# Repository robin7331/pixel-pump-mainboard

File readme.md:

# Pixel Pump Mainboard Rev 8
`KiCad 6.0.11`

See iBOM [rendered as Page](https://htmlpreview.github.io/?https://github.com/robin7331/pixel-pump-mainboard/blob/main/bom/ibom.html) via GitHub Pages

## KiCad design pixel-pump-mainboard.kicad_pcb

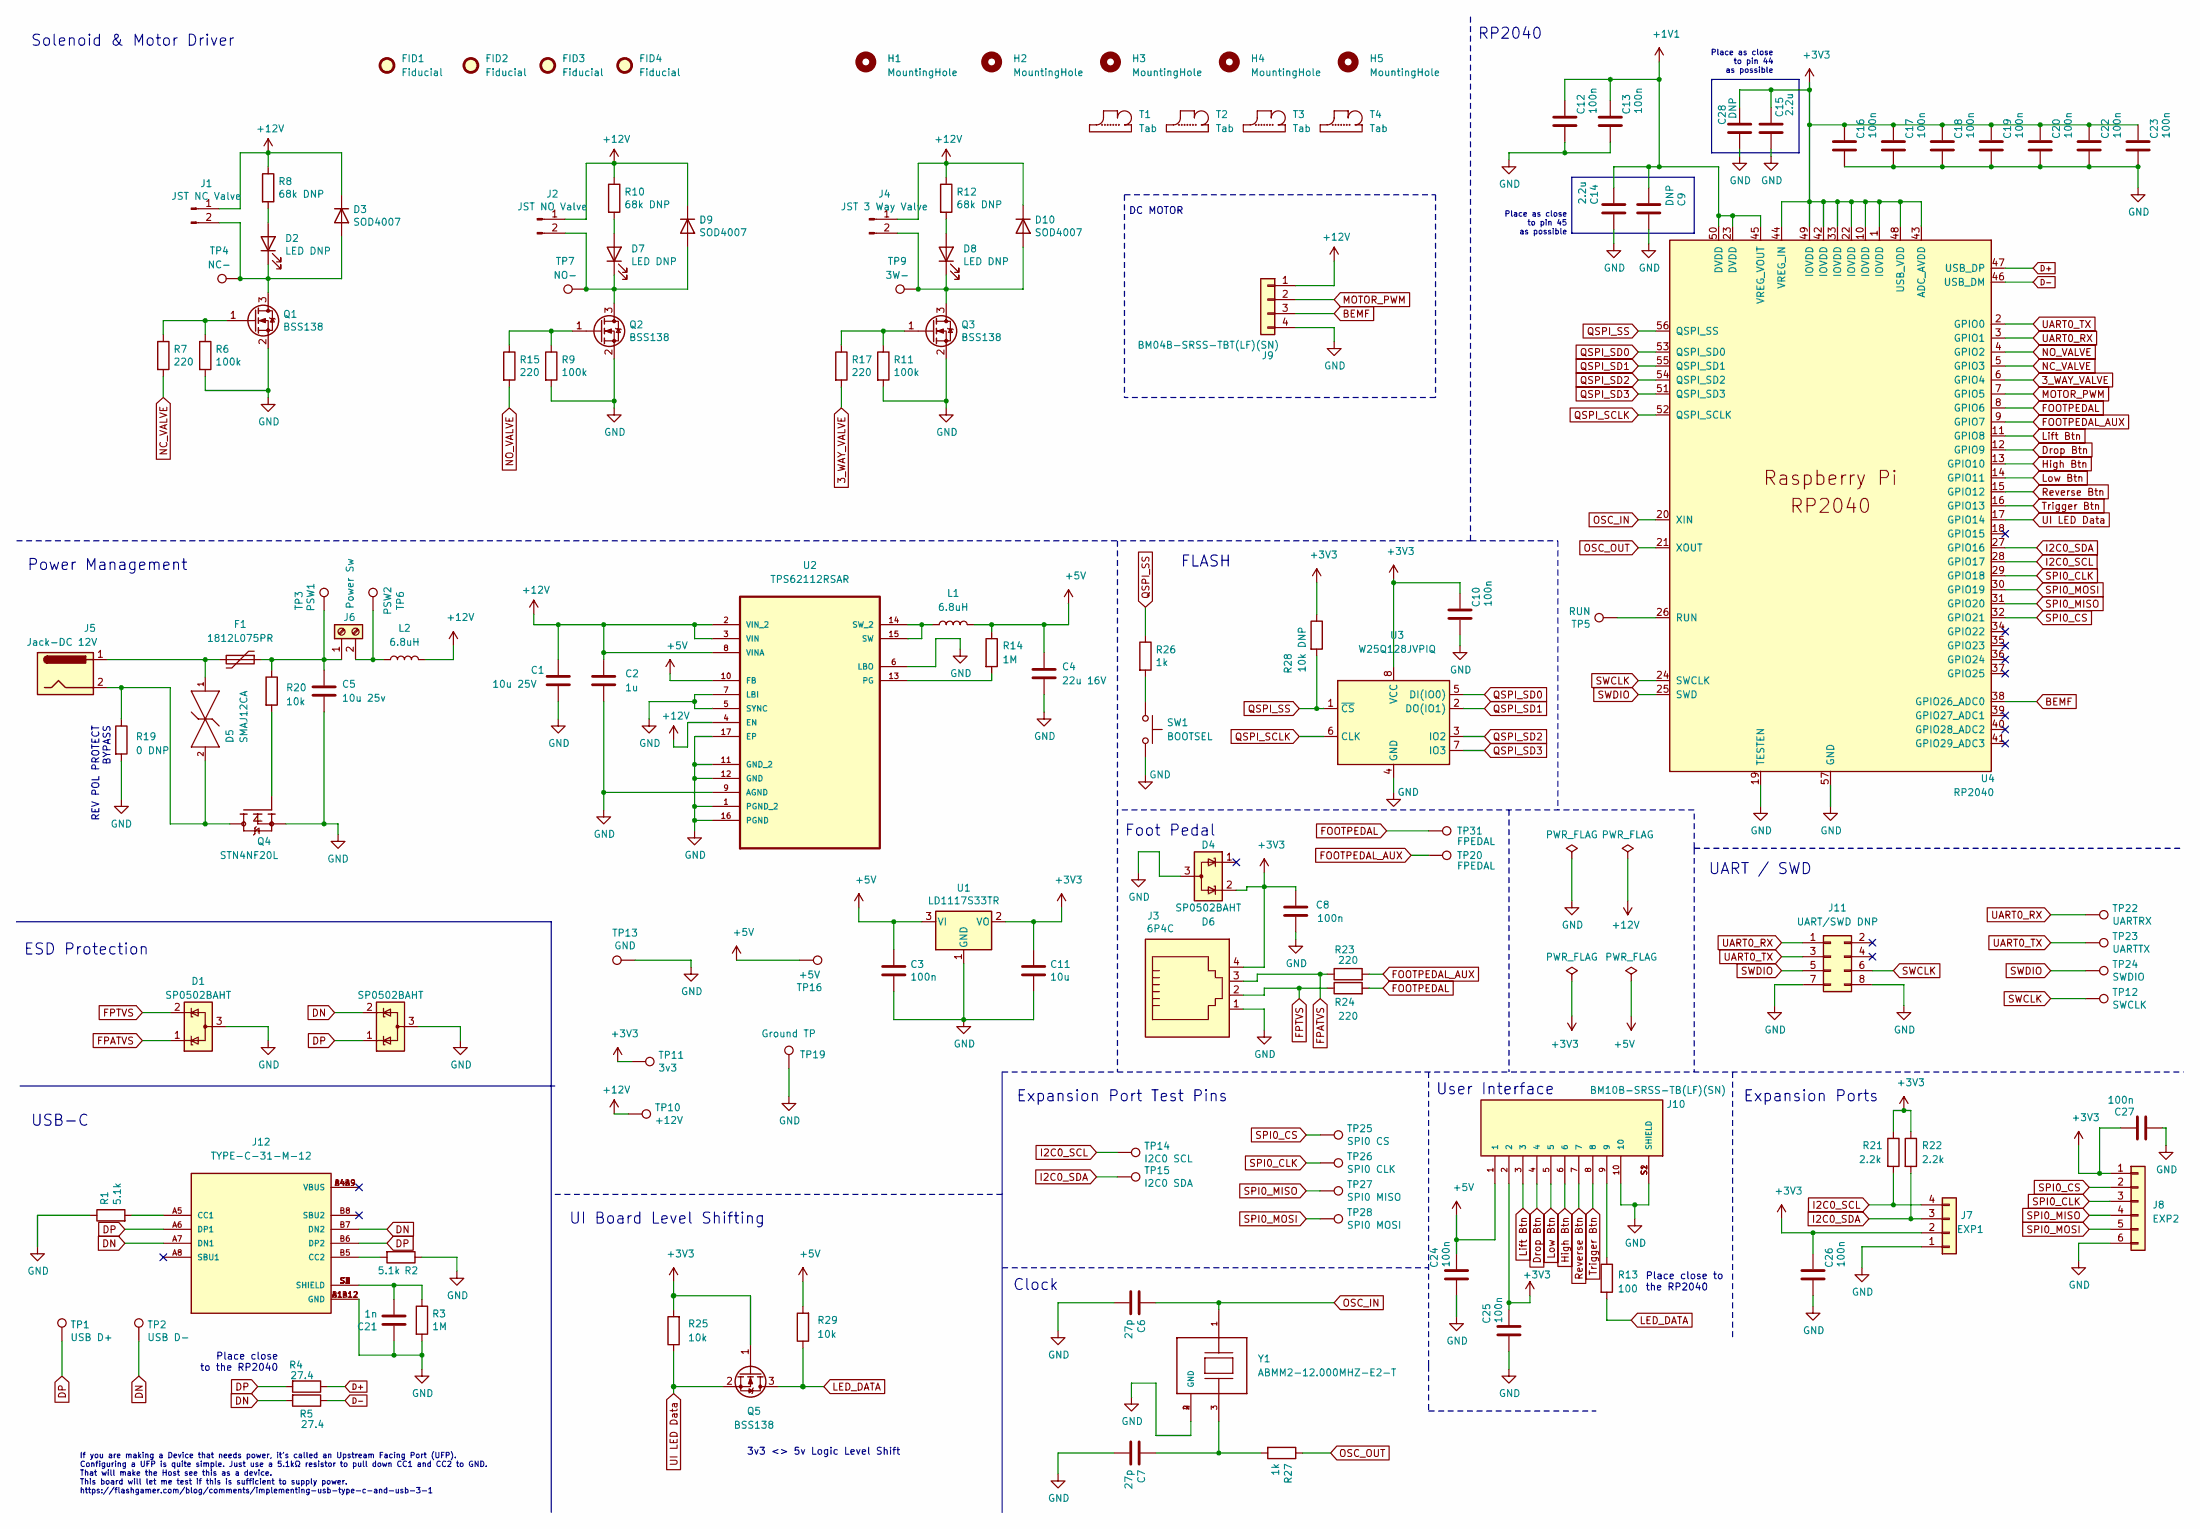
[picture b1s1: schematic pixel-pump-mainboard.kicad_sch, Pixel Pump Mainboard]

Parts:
C1: 10u 25V; C_1210_3225Metric; Part Number C3225X5R1E106K
C2: 1u; C_0805_2012Metric; MPN 1u 0805
C3, C8, C24, C25, C26, C27: 100n; C_0603_1608Metric; MPN 100n 0603
C4: 22u 16V; C_1210_3225Metric; MPN C3225X7R1C226M250AC
C5: 10u 25v; C_1210_3225Metric; Part C3225X5R1E106K
C6, C7: 27p; C_0603_1608Metric; MPN 27p 0603
C9, C28: DNP; C_0402_1005Metric; MPN DNP
C10, C12, C13, C16, C17, C18, C19, C20, C22, C23: 100n; C_0402_1005Metric; MPN 100n 0402
C11: 10u; C_0603_1608Metric; MPN 10u 0603
C14, C15: 2.2u; C_0402_1005Metric; MPN 2.2u 0402
C21: 1n; C_0603_1608Metric; MPN 1n 0603
D1, D4, D6: SP0502BAHT; SOT-23; MPN SP0502BAHT
D2, D7, D8: LED DNP; LED_0603_1608Metric; MPN ORH-G36G DNP
D3, D9, D10: SOD4007; D_SOD-123F; MPN SOD4007
D5: SMAJ12CA; D_SMA; breakdown voltage 13.3V; clamping voltage 19.9V; mouser part number 576-SMAJ12CA; digikey description TVS DIODE 12V 19.9V DO214AC
F1: 1812L075PR; Fuse_1812_4532Metric; MPN 1812L075PR
FID1, FID2, FID3, FID4: Fiducial; Fiducial_0.75mm_Mask1.5mm
H1, H2, H3, H4, H5: MountingHole; MountingHole_3.2mm_M3_Pad_Via
J1: JST NC Valve; JST_XH_B2B-XH-A_1x02_P2.50mm_Vertical; MPN B2B-XH-A-GU
J2: JST NO Valve; JST_XH_B2B-XH-A_1x02_P2.50mm_Vertical; MPN B2B-XH-A-GU
J3: 6P4C; RJ14_Connfly_DS1133-S4_Horizontal; MPN DS1133-S40BPX
J4: JST 3 Way Valve; JST_XH_B2B-XH-A_1x02_P2.50mm_Vertical; MPN B2B-XH-A-GU
J5: Jack-DC 12V; BarrelJack_Wuerth_6941xx301002; MPN 694106301002
J6: Power Sw; TerminalBlock_Phoenix_MKDS-1,5-2-5.08_1x02_P5.08mm_Horizont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; MPN WJ500V-5.08-2P
J7: EXP1; BM04B-SRSS-TBT; MPN BM04B-SRSS-TB(LF)(SN)
J8: EXP2; BM06B-SRSS-TBT; MPN BM06B-SRSS-TB(LF)(SN)
J9: BM04B-SRSS-TBT(LF)(SN); BM04B-SRSS-TBT; MPN BM04B-SRSS-TBT(LF)(SN)
J10: BM10B-SRSS-TB(LF)(SN); PARTREV N/A
J11: UART/SWD DNP; PinHeader_2x04_P2.00mm_Vertical; MPN DNP
J12: TYPE-C-31-M-12; HRO_TYPE-C-31-M-12; PARTREV A
L1, L2: 6.8uH; L_TDK_SLF7032; MPN SLF7032T-6R8M1R6-2-PF
Q1, Q2, Q3: BSS138; SOT-23; MPN BSS138P
Q4: STN4NF20L; SOT223; PARTNO 497-10779-1-ND
Q5: BSS138; SOT-23; MPN BSS138
R1: 5.1k; R_0603_1608Metric; MPN 5.1k 0402
R2: 5.1k; R_0603_1608Metric; MPN 5.1k 0603
R3, R14: 1M; R_0603_1608Metric; MPN 1M 0603
R4, R5: 27.4; R_0402_1005Metric; MPN 27.4 0402
R6, R9, R11: 100k; R_0603_1608Metric; MPN 100k 0603
R7, R15, R17, R23, R24: 220; R_0603_1608Metric; MPN 220 0603
R8, R10, R12: 68k DNP; R_0603_1608Metric; MPN 68k 0603 DNP
R13: 100; R_0603_1608Metric; MPN 100 0603
R19: 0 DNP; R_0805_2012Metric; MPN 0 0805 DNP
R20, R25, R29: 10k; R_0603_1608Metric; MPN 10k 0603
R21, R22: 2.2k; R_0603_1608Metric; MPN 2.2k 0603
R26, R27: 1k; R_0603_1608Metric; MPN 1k 0603
R28: 10k DNP; R_0603_1608Metric; MPN 10k 0603 DNP
SW1: BOOTSEL; SW_Tactile_SKHH_Angled; MPN 1825027-5
T1, T2, T3, T4: Tab
TP1: USB D+; TestPoint_Pad_D2.0mm
TP2: USB D-; TestPoint_Pad_D2.0mm
TP3: PSW1; TestPoint_Pad_D2.0mm
TP4: NC-; TestPoint_Pad_D2.0mm
TP5: RUN; TestPoint_Pad_D2.0mm
TP6: PSW2; TestPoint_Pad_D2.0mm
TP7: NO-; TestPoint_Pad_D2.0mm
TP9: 3W-; TestPoint_Pad_D2.0mm
TP10: +12V; TestPoint_Pad_D2.0mm
TP11: 3v3; TestPoint_Pad_D2.0mm
TP12: SWCLK; TestPoint_Pad_D2.0mm
TP13: GND; TestPoint_Pad_D2.0mm
TP14: I2C0 SCL; TestPoint_Pad_D2.0mm
TP15: I2C0 SDA; TestPoint_Pad_D2.0mm
TP16: +5V; TestPoint_Pad_D2.0mm
TP19: Ground TP; TestPoint_Keystone_5010-5014_Multipurpose
TP20, TP31: FPEDAL; TestPoint_Pad_D2.0mm
TP22: UARTRX; TestPoint_Pad_D2.0mm
TP23: UARTTX; TestPoint_Pad_D2.0mm
TP24: SWDIO; TestPoint_Pad_D2.0mm
TP25: SPI0 CS; TestPoint_Pad_D2.0mm
TP26: SPI0 CLK; TestPoint_Pad_D2.0mm
TP27: SPI0 MISO; TestPoint_Pad_D2.0mm
TP28: SPI0 MOSI; TestPoint_Pad_D2.0mm
U1: LD1117S33TR; SOT-223; MPN LD1117S33TR
U2: TPS62112RSAR; QFN65P400X400X100-17N; MPN TPS62112RSAR
U3: W25Q128JVPIQ; SON127P500X600X80-9N; MPN W25Q128JVPIQ
U4: RP2040; RP2040-QFN-56; MPN RP2040
Y1: ABMM2-12.000MHZ-E2-T; XTAL_ABMM2-12.000MHZ-E2-T; PARTREV 01.18.13

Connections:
3_WAY_VALVE: R17.2, U4.6 (GPIO4)
+1V1: C9.1, C12.2, C13.2, C14.1, U4.23 (DVDD), U4.45 (VREG_VOUT), U4.50 (DVDD)
+3V3: C8.2, C10.2, C11.1, C15.1, C16.2, C17.2, C18.2, C19.2, C20.2, C22.2, C23.2, C25.2, C26.2, C27.2, C28.1, D6.2 (K), J3.4, J7.2, J8.1, J10.2, Q5.1 (G), R21.1, R22.1, R25.2, R28.1, TP11.1, U1.2 (VO), U3.8 (VCC), U4.1 (IOVDD), U4.10 (IOVDD), U4.22 (IOVDD), U4.33 (IOVDD), U4.42 (IOVDD), U4.43 (ADC_AVDD), U4.44 (VREG_IN), U4.48 (USB_VDD), U4.49 (IOVDD)
+5V: C3.1, C4.1, C24.2, J10.1, L1.2, R14.1, R29.2, TP16.1, U1.3 (VI), U2.10 (FB)
+12V: C1.1, C2.1, D3.1 (K), D9.1 (K), D10.1 (K), J1.1, J2.1, J4.1, J9.1, L2.2, R8.1, R10.1, R12.1, TP10.1, U2.2 (VIN_2), U2.3 (VIN), U2.4 (EN), U2.8 (VINA)
BEMF: J9.3, U4.38 (GPIO26_ADC0)
D+: R4.1, U4.47 (USB_DP)
D-: R5.1, U4.46 (USB_DM)
DN: D4.2 (K), J12.A7 (DN1), J12.B7 (DN2), R5.2, TP2.1
DP: D4.1 (K), J12.A6 (DP1), J12.B6 (DP2), R4.2, TP1.1
Drop Btn: J10.4, U4.12 (GPIO9)
FOOTPEDAL: R24.2, TP31.1, U4.8 (GPIO6)
FOOTPEDAL_AUX: R23.2, TP20.1, U4.9 (GPIO7)
FPATVS: D1.1 (K), J3.3, R23.1
FPTVS: D1.2 (K), J3.2, R24.1
GND: C1.2, C2.2, C3.2, C4.2, C5.2, C6.2, C7.2, C8.1, C9.2, C10.1, C11.2, C12.1, C13.1, C14.2, C15.2, C16.1, C17.1, C18.1, C19.1, C20.1, C21.1, C22.1, C23.1, C24.1, C25.1, C26.1, C27.1, C28.2, D1.3 (A), D4.3 (A), D6.3 (A), J3.1, J7.1, J8.6, J9.4, J10.10, J10.S1 (SHIELD), J10.S2 (SHIELD), J11.7, J11.8, J12.A1B12 (GND), J12.B1A12 (GND), Q1.2 (S), Q2.2 (S), Q3.2 (S), Q4.3, R1.1, R2.1, R3.2, R6.2, R9.2, R11.2, R19.2, SW1.2, TP13.1, TP19.1, U1.1 (GND), U2.1 (PGND_2), U2.5 (SYNC), U2.6 (LBO), U2.7 (LBI), U2.9 (AGND), U2.11 (GND_2), U2.12 (GND), U2.16 (PGND), U2.17 (EP), U3.4 (GND), U4.19 (TESTEN), U4.57 (GND), Y1.2 (GND), Y1.4 (GND)
High Btn: J10.6, U4.13 (GPIO10)
I2C0_SCL: J7.4, R21.2, TP14.1, U4.28 (GPIO17)
I2C0_SDA: J7.3, R22.2, TP15.1, U4.27 (GPIO16)
LED_DATA: Q5.3 (D), R13.2, R29.1
Lift Btn: J10.3, U4.11 (GPIO8)
Low Btn: J10.5, U4.14 (GPIO11)
MOTOR_PWM: J9.2, U4.7 (GPIO5)
NC_VALVE: R7.2, U4.5 (GPIO3)
NO_VALVE: R15.2, U4.4 (GPIO2)
unnamed: C5.1, F1.1, J6.1, R20.1, TP3.1
unnamed: C7.1, R27.2, Y1.3
unnamed: C21.2, J12.S1 (SHIELD), J12.S2 (SHIELD), J12.S3 (SHIELD), J12.S4 (SHIELD), R3.1
unnamed: D2.1 (K), D3.2 (A), J1.2, Q1.3 (D), TP4.1
unnamed: D2.2 (A), R8.2
unnamed: D5.1, F1.2, J5.1
unnamed: D5.2, J5.2, Q4.2, Q4.T, R19.1
unnamed: D7.1 (K), D9.2 (A), J2.2, Q2.3 (D), TP7.1
unnamed: D7.2 (A), R10.2
unnamed: D8.2 (A), R12.2
unnamed: D8.1 (K), D10.2 (A), J4.2, Q3.3 (D), TP9.1
unnamed: J6.2, L2.1, TP6.1
unnamed: J10.9, R13.1
unnamed: J12.A5 (CC1), R1.2
unnamed: J12.B5 (CC2), R2.2
unnamed: L1.1, U2.14 (SW_2), U2.15 (SW)
unnamed: Q1.1 (G), R6.1, R7.1
unnamed: Q2.1 (G), R9.1, R15.1
unnamed: Q3.1 (G), R11.1, R17.1
unnamed: Q4.1, R20.2
unnamed: R14.2, U2.13 (PG)
unnamed: R26.2, SW1.1
unnamed: TP5.1, U4.26 (RUN)
OSC_IN: C6.1, U4.20 (XIN), Y1.1
OSC_OUT: R27.1, U4.21 (XOUT)
QSPI_SCLK: U3.6 (CLK), U4.52 (QSPI_SCLK)
QSPI_SD0: U3.5 (DI(IO0)), U4.53 (QSPI_SD0)
QSPI_SD1: U3.2 (DO(IO1)), U4.55 (QSPI_SD1)
QSPI_SD2: U3.3 (IO2), U4.54 (QSPI_SD2)
QSPI_SD3: U3.7 (IO3), U4.51 (QSPI_SD3)
QSPI_SS: R26.1, R28.2, U3.1 (~CS), U4.56 (QSPI_SS)
Reverse Btn: J10.7, U4.15 (GPIO12)
SPI0_CLK: J8.3, TP26.1, U4.29 (GPIO18)
SPI0_CS: J8.2, TP25.1, U4.32 (GPIO21)
SPI0_MISO: J8.4, TP27.1, U4.31 (GPIO20)
SPI0_MOSI: J8.5, TP28.1, U4.30 (GPIO19)
SWCLK: J11.6, TP12.1, U4.24 (SWCLK)
SWDIO: J11.5, TP24.1, U4.25 (SWD)
Trigger Btn: J10.8, U4.16 (GPIO13)
UART0_RX: J11.1, TP22.1, U4.3 (GPIO1)
UART0_TX: J11.3, TP23.1, U4.2 (GPIO0)
UI LED Data: Q5.2 (S), R25.1, U4.17 (GPIO14)

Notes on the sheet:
ESD Protection
FLASH
Clock
REV POL PROTECT BYPASS
DC MOTOR
Place close to the RP2040
UART / SWD
Expansion Port Test Pins
Place as close to pin 45 as possible
Power Management
Solenoid & Motor Driver
RP2040
User Interface
Place close to the RP2040
If you are making a Device that needs power, it’s called an Upstream Facing Port (UFP). Configuring a UFP is quite simple. Just use a 5.1kΩ resistor to pull down CC1 and CC2 to GND. That will make the Host see this as a device. This board will let me test if this is sufficient to supply power. http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
UI Board Level Shifting
3v3 <> 5v Logic Level Shift
Foot Pedal
USB-C
Place as close to pin 44 as possible
Expansion Ports

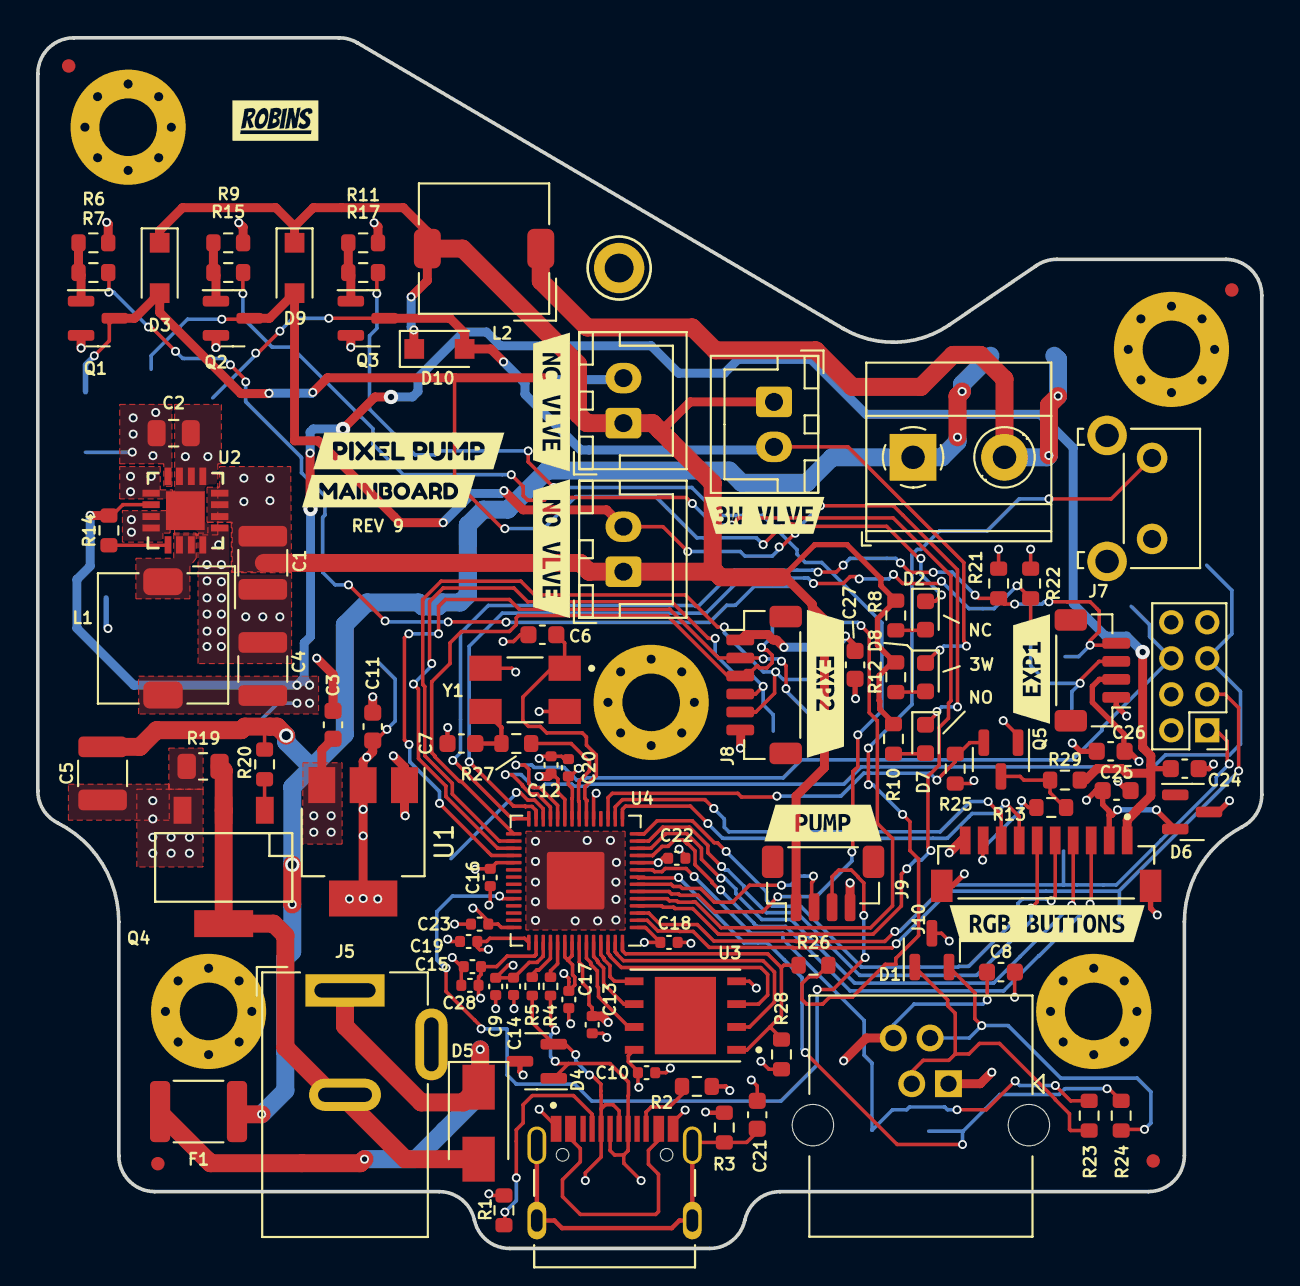
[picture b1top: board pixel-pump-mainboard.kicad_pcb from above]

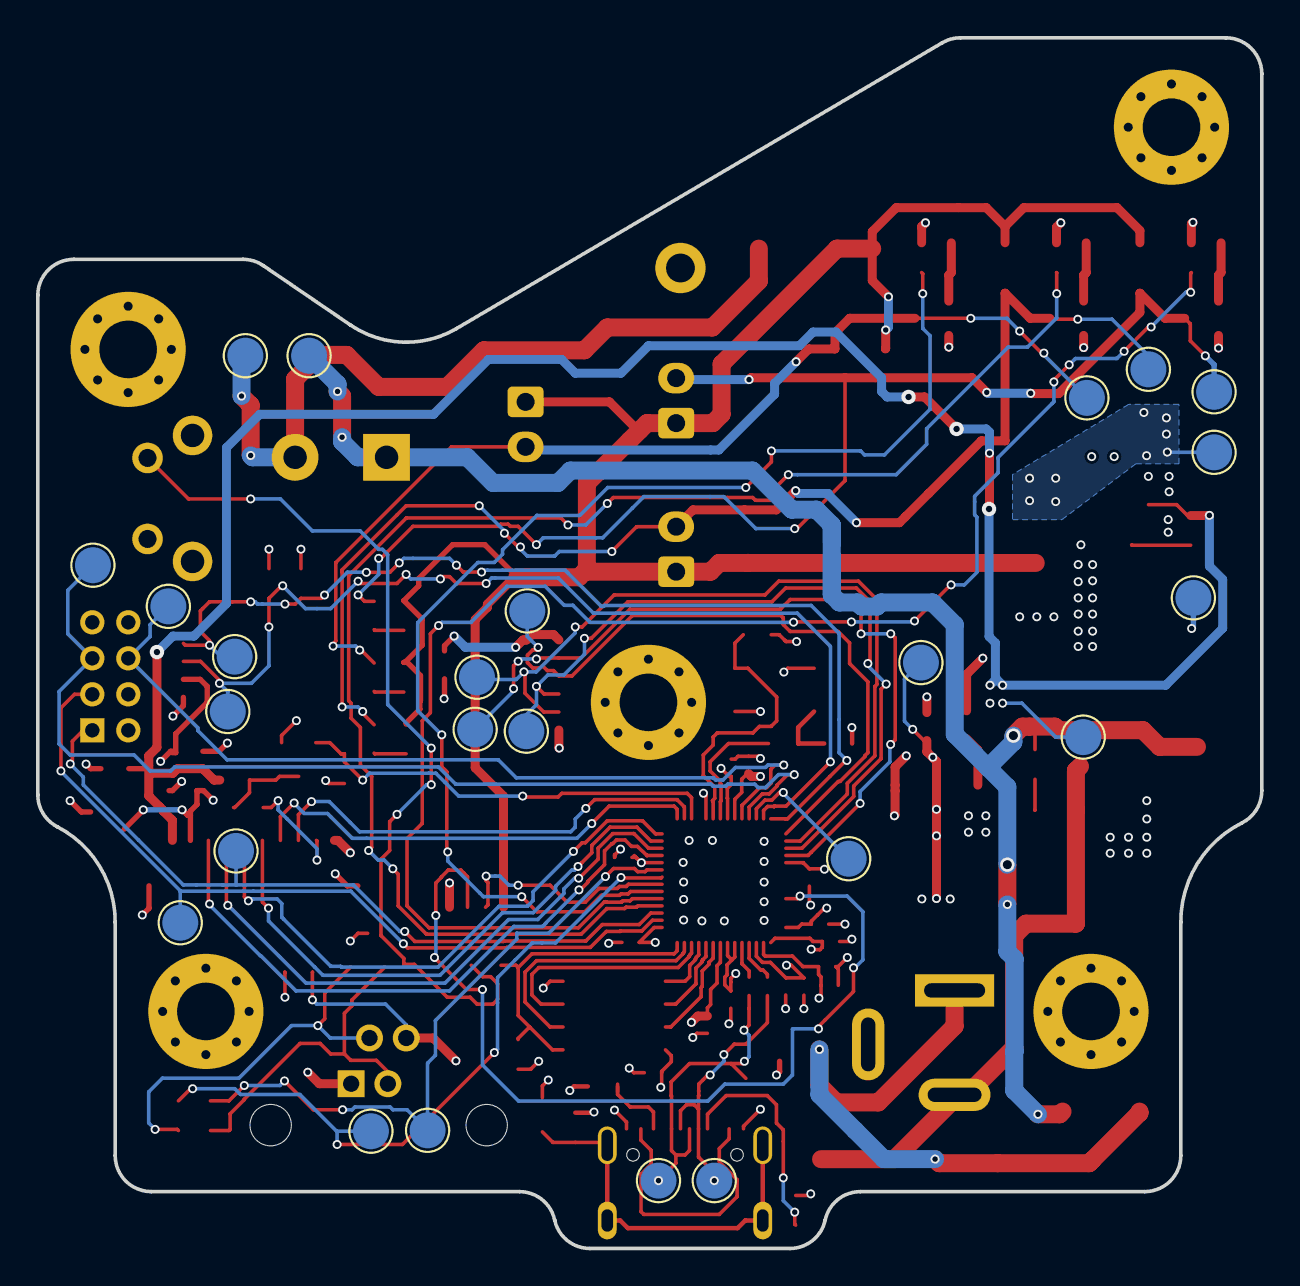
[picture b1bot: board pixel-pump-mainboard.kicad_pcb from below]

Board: 4 copper layers, 68.0 x 67.3 mm, 138 parts (24 on the bottom side), 67 nets.

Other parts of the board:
kibuzzard-62EBC211: G***; kibuzzard-62EBC211
kibuzzard-62EBC230: G***; kibuzzard-62EBC230
kibuzzard-626BB8E0: G***; kibuzzard-626BB8E0
kibuzzard-626BB906: G***; kibuzzard-626BB906
kibuzzard-6107E0E1: G***; kibuzzard-6107E0E1
kibuzzard-6107E4A2: G***; kibuzzard-6107E4A2
kibuzzard-6107E44E: G***; kibuzzard-6107E44E
kibuzzard-6107E45C: G***; kibuzzard-6107E45C
kibuzzard-6107E302: G***; kibuzzard-6107E302

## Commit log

2020-12-17 initial
2020-12-17 added gitignore
2020-12-18 schematics finished
2020-12-21 schematics done
2020-12-22 another wip
2020-12-22 routing finished
2020-12-22 added molex
2020-12-22 last changes and gerber files generated
2020-12-22 added ibom
2021-01-14 Ignore step files
2021-01-14 Cleanup values
2021-01-14 Fix wrong boost feedback voltage divider resistors
2021-01-14 Dim LEDs by increasing their resistor values
2021-01-14 Fix both fuse footprints (they were swapped)
2021-01-14 Generate iBom
2021-01-14 Update silkscreen labels
2021-03-03 Add DXF files from fusion
2021-03-08 remove old files
2021-03-08 Add backups to .gitignore
2021-03-08 Finished schematics
2021-03-09 finished schematics and assigned footprints
2021-03-09 Remove old PCB
2021-03-09 Initial PCB
2021-03-09 Update USB-C
2021-03-09 Updated PCB
2021-03-09 Edge cuts update
2021-03-09 Placed components
2021-03-09 pcb layout finished
2021-03-09 Adjusted board thickness to be 1.6mm
2021-03-10 Generate gerbers
2021-03-11 Generated Gerbers
2021-03-27 Create schematic PDF
2021-05-17 STM32 version
2021-05-17 Change DC-DC 5V converter to TPS561201DDCR
2021-05-17 Change from STM32 to RP2040
2021-05-17 Cleanup
2021-05-17 Assign or update remaining footprints
2021-05-17 Update crystal and footprints of components
2021-05-19 RP2040 PCB routed
2021-05-19 Add fiducials
2021-05-20 Updated min via drill and pad size
2021-08-02 Change various things
2021-08-02 Bump rev to 2
2021-08-02 Assign footprints
2021-08-02 WiP updating footprints
2021-08-02 Updated kicad nightly
2021-08-02 WiP Layout Ref 2
2021-08-02 Finished Ref 2 layout
2021-08-02 Update passives around RP2040
2021-08-02 Add UI board level shifting
2021-08-02 Updated pad below RP2040
2021-08-03 Changed Buck Converter
2021-08-03 Add missing components
2021-08-03 Minor upgrades
2021-08-03 Remove old schematics
2021-08-03 Add dxf import documentation
2021-08-03 Plot board
2021-08-03 Update footprints and generate new iBOM
2021-08-06 Changed part no and regenerated iBOM
2021-08-06 Generate rev 2 gerbers
2021-11-19 Rename entire project to pixel pump
2021-11-19 Clean footprint library
2021-11-19 Cleanup board libraries
2021-11-19 Remove old dependency
2021-11-19 Add readme
2021-11-21 Add PDF/PNG schematic
2022-01-10 Upgrade to Kicad 6
2022-01-11 Updated schematic for EMI compliance
2022-01-11 Minor Rev 3 changes
2022-01-11 Minor things fixed
2022-01-12 ERC & Assigned footprints
2022-01-12 Updated layout for EMI specific changes
2022-01-14 Finish EMI changes
2022-01-14 Remove old gerbers
2022-01-14 Add panel-output to gitignore
2022-01-14 Update iBOM
2022-01-14 Adjusted spacing between testpoints
2022-01-14 Add panelize scripts
2022-01-14 Update gitignore
2022-01-15 Update panel script
2022-01-15 Add automatic gerber creation to build scriot
2022-01-16 Cleanup dxf files
2022-01-16 Remove rescue lib and dcm
2022-04-29 Rename ports to EXP1 and EXP2 and reduce mousebite stiffness
2022-05-23 Switch to CTS 445C25D12M00000 12 MHz crystal
2022-07-25 Revert back to ABM12 footprint
2022-08-04 Assign all MPNs
2022-08-04 Add robins logo
2022-08-04 Change appearance of labels
2022-08-04 Change appearance of labels (again)
2022-12-03 Add iBOM Github Pages Link to Readme.md
2022-12-22 iBOM
2023-01-09 Remove *.csv from gitignore
2023-01-09 Add essemtec pnp csv file
2023-01-09 Fix USB position in pnp csv
2023-01-12 Correctly rotate LDO
2023-01-30 Add fiducials and fix THT parts to be SMD
2023-01-30 Bump rev to 8
2023-01-31 Remove DNP parts from BOM, increase Fiducial to 0.75/1.5mm
2023-01-31 Add Aisler Bridge marks
2023-01-31 Update Aisler bridge locations
2023-01-31 Update Aisler bridge lines
2023-02-10 Remove Aisler Outline markers
2023-02-11 Add KiKit annotations
2023-02-13 Remove gerbers from gitignore
2023-02-13 Rev 8 panel settings and export
2023-02-13 Remove SVG from readme
2023-02-24 Fixed issues and generated the final pos file
2023-02-24 Rev 9
2023-02-24 Update panelize preset
2023-02-24 Panelize Rev 9
2023-02-24 Fix fiducial positions
2023-02-24 Change kikit mouebite width to 2mm
2023-02-24 Panelized again :/
